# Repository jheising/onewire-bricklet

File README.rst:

Temperature Bricklet
====================

This repository contains the firmware source code and the hardware design
files. The documentation generator configs can be found at
https://github.com/Tinkerforge/generators

Repository Content
------------------

software/:
 * examples/: Examples for all supported languages
 * build/: Makefile and compiled files
 * src/: Source code of firmware
 * generate_makefile: Shell script to generate Makefile from cmake script

hardware/:
 * Contains kicad project files and additionally schematics as pdf

datasheets/:
 * Contains datasheets for sensors and complex ICs that are used

Hardware
--------

The hardware is designed with the open source EDA Suite KiCad
(http://www.kicad-pcb.org). Before you are able to open the files,
you have to install the Tinkerforge kicad-libraries
(https://github.com/Tinkerforge/kicad-libraries). You can either clone
them directly in hardware/ or clone them in a separate folder and
symlink them into hardware/
(ln -s kicad_path/kicad-libraries project_path/hardware). After that you
can open the .pro file in hardware/ with kicad and from there view and
modify the schematics and the PCB layout.

Software
--------

To compile the C code we recommend you to install the newest CodeSourcery ARM
EABI GCC compiler
(https://sourcery.mentor.com/sgpp/lite/arm/portal/subscription?@template=lite).
You also need to install bricklib (https://github.com/Tinkerforge/bricklib)
and brickletlib (https://github.com/Tinkerforge/brickletlib).
You can either clone them directly in software/src/ or clone them in a
separate folder and symlink them into software/src/
(ln -s bricklib_path/bricklib project_path/software/src/). Finally make sure to
have CMake installed (http://www.cmake.org/cmake/resources/software.html).

After that you can generate a Makefile from the cmake script with the
generate_makefile shell script (in software/) and build the firmware
by invoking make in software/build/. The firmware (.bin) can then be found
in software/build/ and uploaded with brickv (click button "Flashing"
on start screen).

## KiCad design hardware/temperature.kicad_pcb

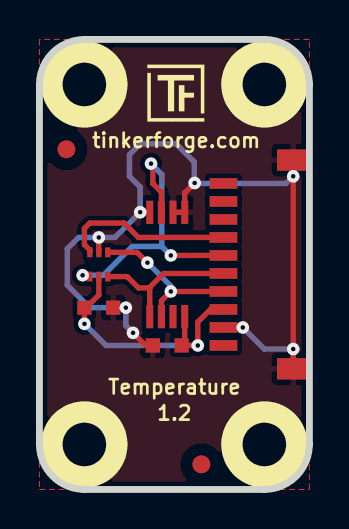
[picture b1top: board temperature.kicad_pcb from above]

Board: 2 copper layers, 15.0 x 25.0 mm, 14 parts (0 on the bottom side), 6 nets.

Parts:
C1, C2: 100nF; C0603
Fiducial_Mark: VAL**; Fiducial_Mark
Fiducial_Mark#2: VAL**; Fiducial_Mark
P1: CON-SENSOR
Ref**: Val**; Logo_31x31
U1: M24C64; TSSOP8
U2: TMP102; SOT563
U3, U4, U5, U6: DRILL; DRILL_NP
VAL: CE_5mm
VAL#2: WEEE_7mm

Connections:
ALERT: P1.7, U2.3
GND: C1.2, C2.2, P1.2, P1.EP, U1.1, U1.2, U1.4, U2.2
unnamed: P1.6, U1.3, U2.4
SCL: P1.4, U1.6, U2.1
SDA: P1.5, U1.5, U2.6
VCC: C1.1, C2.1, P1.3, U1.8, U2.5

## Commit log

2011-08-25 initial hardware source commit
2011-08-25 add project description
2011-09-13 add java bindings and examples
2011-09-13 remove wrong binding java binding
2011-09-14 limit line length of java examples to 100 characters
2011-09-23 Add C# examples and bindings
2011-10-05 Remove Bindings and IP Connection (these are generated and they change too often) and rename bindings to examples
2011-10-05 add tinkerforge package to python imports
2011-10-06 remove faulty gcc commandline invocation
2011-10-06 add firmware version and name
2012-02-13 checkin of version 1.1: - remove address line resistor - add fiducials on board
2012-02-14 add compatability for different tick types
2012-02-15 Add changelog
2012-03-21 Use timeout for i2c mutex, otherwise Temperature Bricklet does not work w ith IMU Brick
2012-04-25 Unify capitalization of "IP connection" in examples
2012-05-09 Add PHP examples
2012-05-14 java: Remove unnecessary new String(...) calls
2012-05-25 Add Ruby examples
2012-06-05 Fix register_callback syntax error in Ruby examples on Windows
2012-06-12 Use correct term 'Bricklet' in example code error message
2012-06-12 Prefer IPConnection destroy over join_thread
2012-07-01 Add generate_makefile.bat for windows
2012-07-25 Add Delphi examples
2012-08-08 delphi: Add comment about UID
2012-10-24 Make cmake find the correct objcopy binary
    On some systems cmake uses the wrong objcopy binary, tell it to use
    the correct one.
2012-11-13 Support for protocol 2.0
2012-11-29 Make examples compatible to Protocol V2.0
2012-11-29 Make Ruby examples Protocol 2.0 compatible
2012-11-29 Make C examples Protocol 2.0 compatible
2012-11-29 Make Java examples Protocol 2.0 compatible
2012-11-29 Make PHP examples Protocol 2.0 compatible
2012-11-29 Make Delphi/Pascal examples Protocol 2.0 compatible
2012-11-30 delphi: Remove unnecessary parentheses and call destructor again
2012-12-05 Add protocol 2.0 compatability to C# bindings
2012-12-06 Fix C examples
2012-12-11 Avoid g++ warnings about missing casts in C examples
2012-12-18 Add .gitignore
2013-01-09 Use specific device object for callbacks
2013-01-15 Turn debugging off
2013-01-17 Make Java examples compatible to new listener approach
2013-01-28 Update outdated comment in Java example
2013-02-07 Use IPconnection disconnect explicitly in examples
2013-02-14 Fix debounce period in C# threshold example
2013-02-18 Add Visual Basic .NET examples
2013-03-26 Add I2C Mode switch API
2013-03-26 Add changelog for 2.0.1
2013-08-14 Add shell examples
2013-08-21 windows: Don't trigger a build in generate_makefile.bat
    Also use normal make instead of a special named one.
2013-12-19 Fix wrong length for GetDebounce packet (through brickletlib)
2014-01-06 Add static assert for BrickContext size
2014-01-10 Add Perl examples
2014-01-15 php: Use const for constant values
2014-02-07 Add Mathematica examples
2014-02-07 mathematica: Add another example
2014-02-07 mathematica: Avoid {{ because the website template system will interpret it as broken placeholder
2014-02-10 perl: fixed namespace
2014-02-12 javascript: add examples
2014-02-18 javascript: examples fixed
2014-02-20 javascript: add html examples
2014-02-24 javascript: port 4280, startExample()
2014-02-28 javascript: Break long lines and cleanup whitespace
2014-03-04 Fix typos
2014-03-05 Add LabVIEW examples
2014-03-06 labview: Add examples in LV2010 format
2014-03-26 matlab: add examples
2014-04-02 java: Unify constants style
2014-04-02 perl: Unify print style
2014-04-17 matlab: Adapt examples to new callback style
2014-04-17 matlab: Add parentheses to make pygments happy
2014-07-15 java: Replace System.console() usage with an Eclipse compatible pattern
2014-12-02 Use ReadLine instead of ReadKey for C# example
2014-12-31 change in i2c handling: detect communication problems and return -99.99°C instead of busy waiting
2015-01-06 Add version 2.0.3 changelog
2015-02-13 vbnet: Use ReadLine instead of ReadKey
    Because ReadKey doesn't work with a pipe as stdin on the RED Brick.
2015-03-02 windows: Stop cmake from searching for mingw32-make.exe
    Using MinGW Makefiles as generator makes cmake search for mingw32-make.exe
    which might not be installed because GnuWin32's make.exe is used instead.
2015-03-26 update hardware files to current version
2015-04-09 c: Whitespace
2015-06-24 javascript: Clean up output creation
2015-06-29 octave: Handle short difference between Octave 3.6 and 3.8
    In Octave 3.6 a short is not automatically handled as a number.
2015-07-25 Make JavaScript browser example textarea readonly
2015-07-27 Cleanup C/C++, C#, Java, Python and Ruby examples
2015-07-29 Reformat changelog
2015-07-30 Fix typo
2015-08-07 Use full device class name in Python examples
2015-08-12 Fix minor warnings in C/C++ examples
2015-08-14 Cleanup Delphi examples
2015-08-18 Cleanup VB.NET examples
2015-08-19 Cleanup Perl examples
2015-08-21 Prefer printf over puts in C/C++ examples
2015-09-09 Duplicate cmake call to fix bug during cmake creation
2015-09-15 mathematica: Add missing comment
2015-09-30 Generator based example cleanup
2015-11-12 matlab: Fix callback handling for R2014a
    http://undocumentedmatlab.com/blog/matlab-callbacks-for-java-events-in-r2014a
2015-11-25 Include date and commit into changelog
2016-03-02 update silkscreen
2016-05-18 c: Add missing device destroy call
2016-07-01 Make the change UID comment more explicit
2017-04-13 csharp: Adapt example
2017-04-21 shell: Adapt example
2017-06-02 octave: Use javaObject instead of deprecated java_new
2017-08-04 add missing pcb
2017-08-04 Add 3d information (final)
2017-08-04 Add 3d model (*.step & *.FCStd)
2018-05-03 Support for changing resolution

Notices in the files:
hardware/temperature.kicad_pcb:
Licensed under CERN OHL v.1.1
Copyright (©) 2011, B.Nordmeyer
Copyright Tinkerforge GmbH 2011.
This documentation describes Open Hardware and is licensed under the
CERN OHL v. 1.1.
